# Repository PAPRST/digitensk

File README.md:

# Digital Ten GHz Super Keyer
Modern system for digital mode on 6 and 3cm HAM band

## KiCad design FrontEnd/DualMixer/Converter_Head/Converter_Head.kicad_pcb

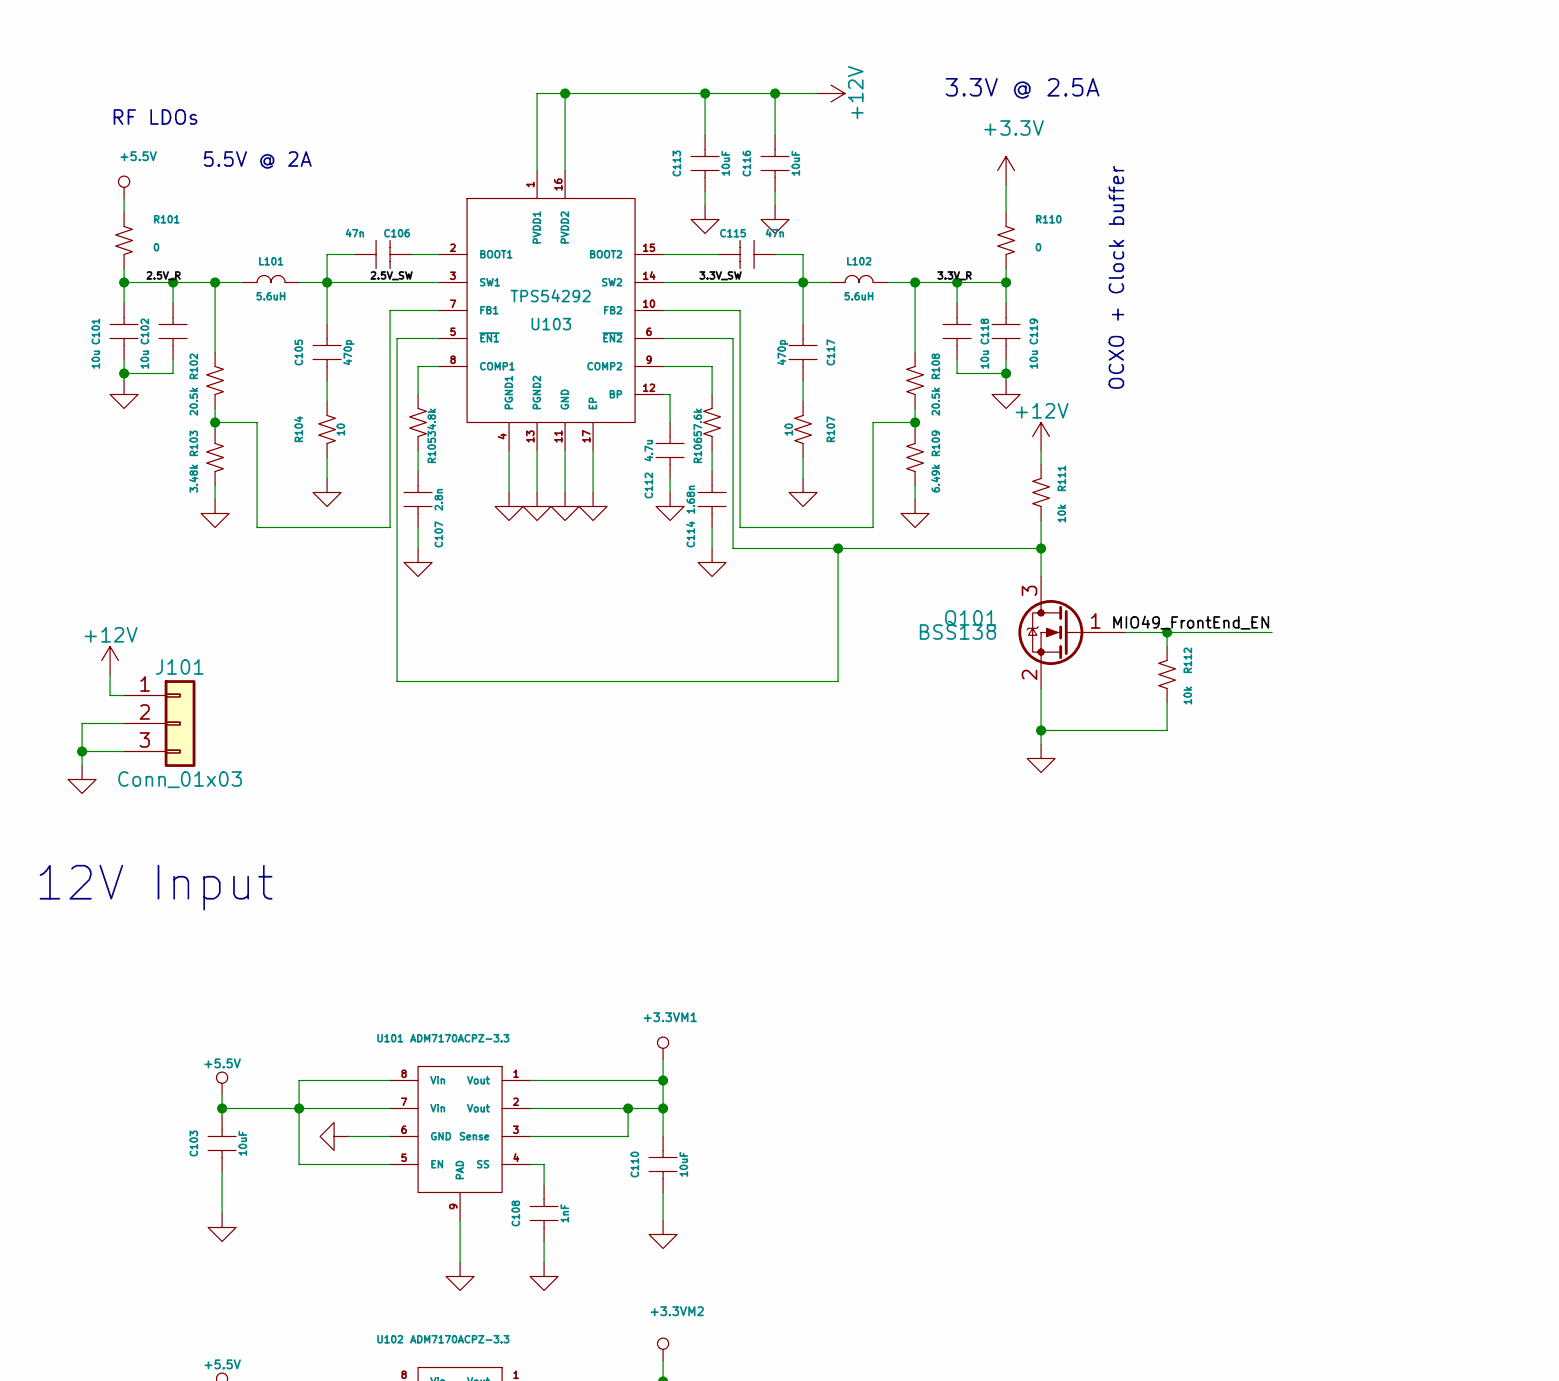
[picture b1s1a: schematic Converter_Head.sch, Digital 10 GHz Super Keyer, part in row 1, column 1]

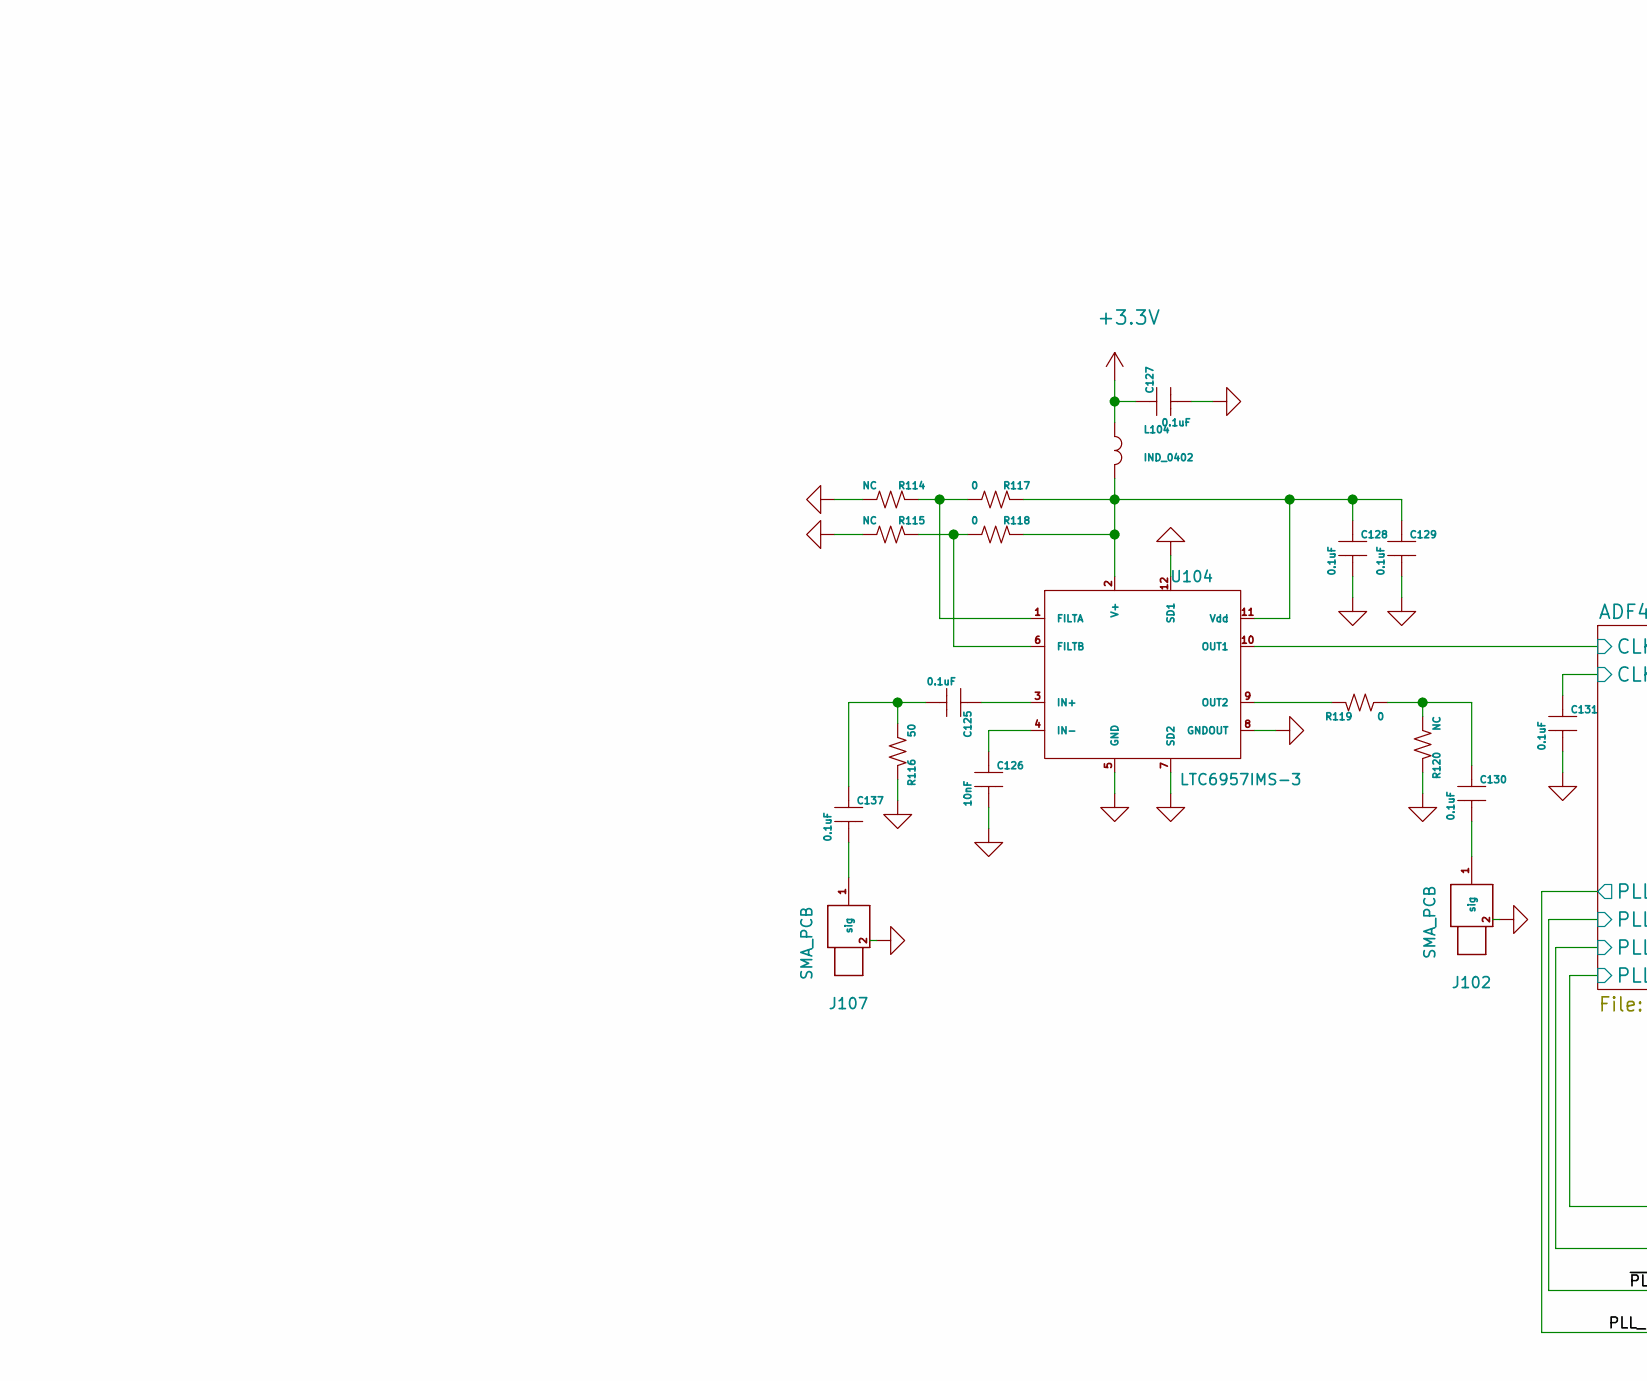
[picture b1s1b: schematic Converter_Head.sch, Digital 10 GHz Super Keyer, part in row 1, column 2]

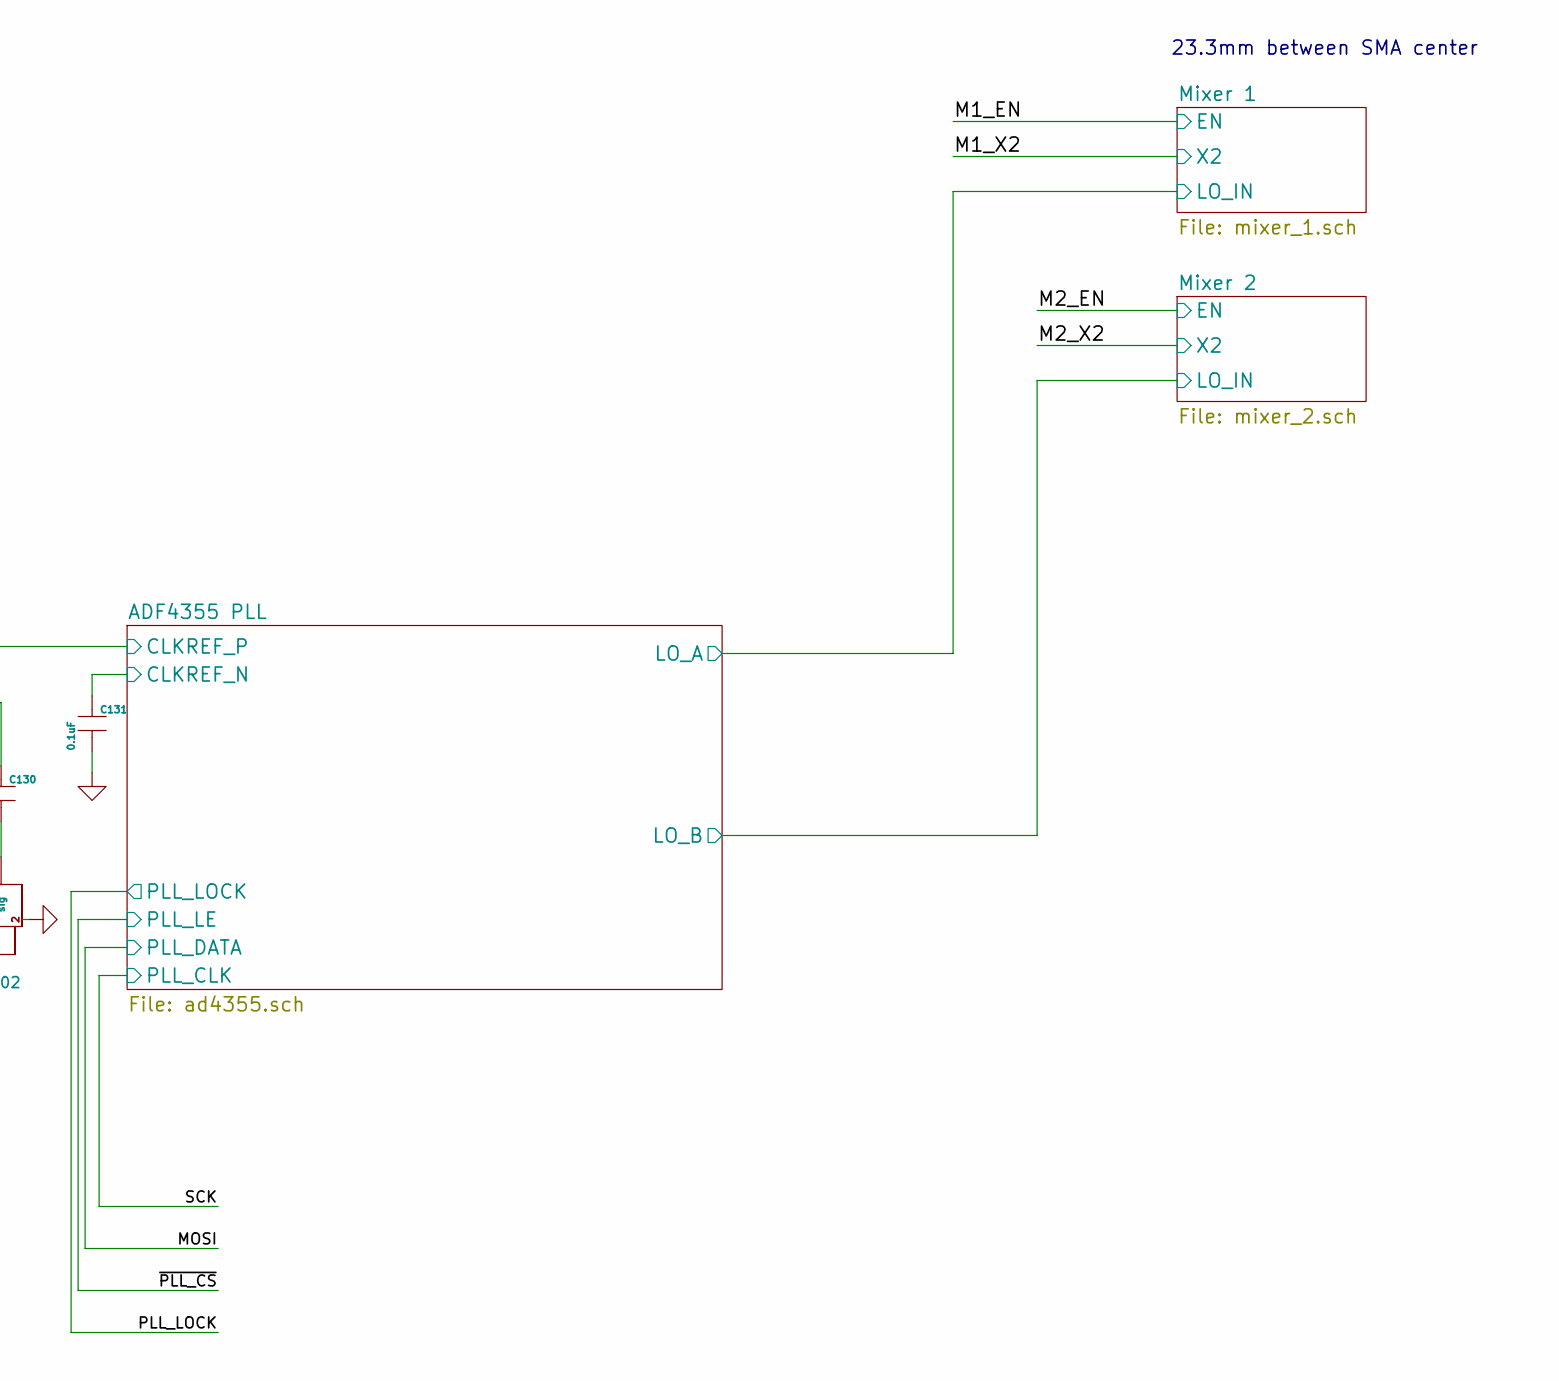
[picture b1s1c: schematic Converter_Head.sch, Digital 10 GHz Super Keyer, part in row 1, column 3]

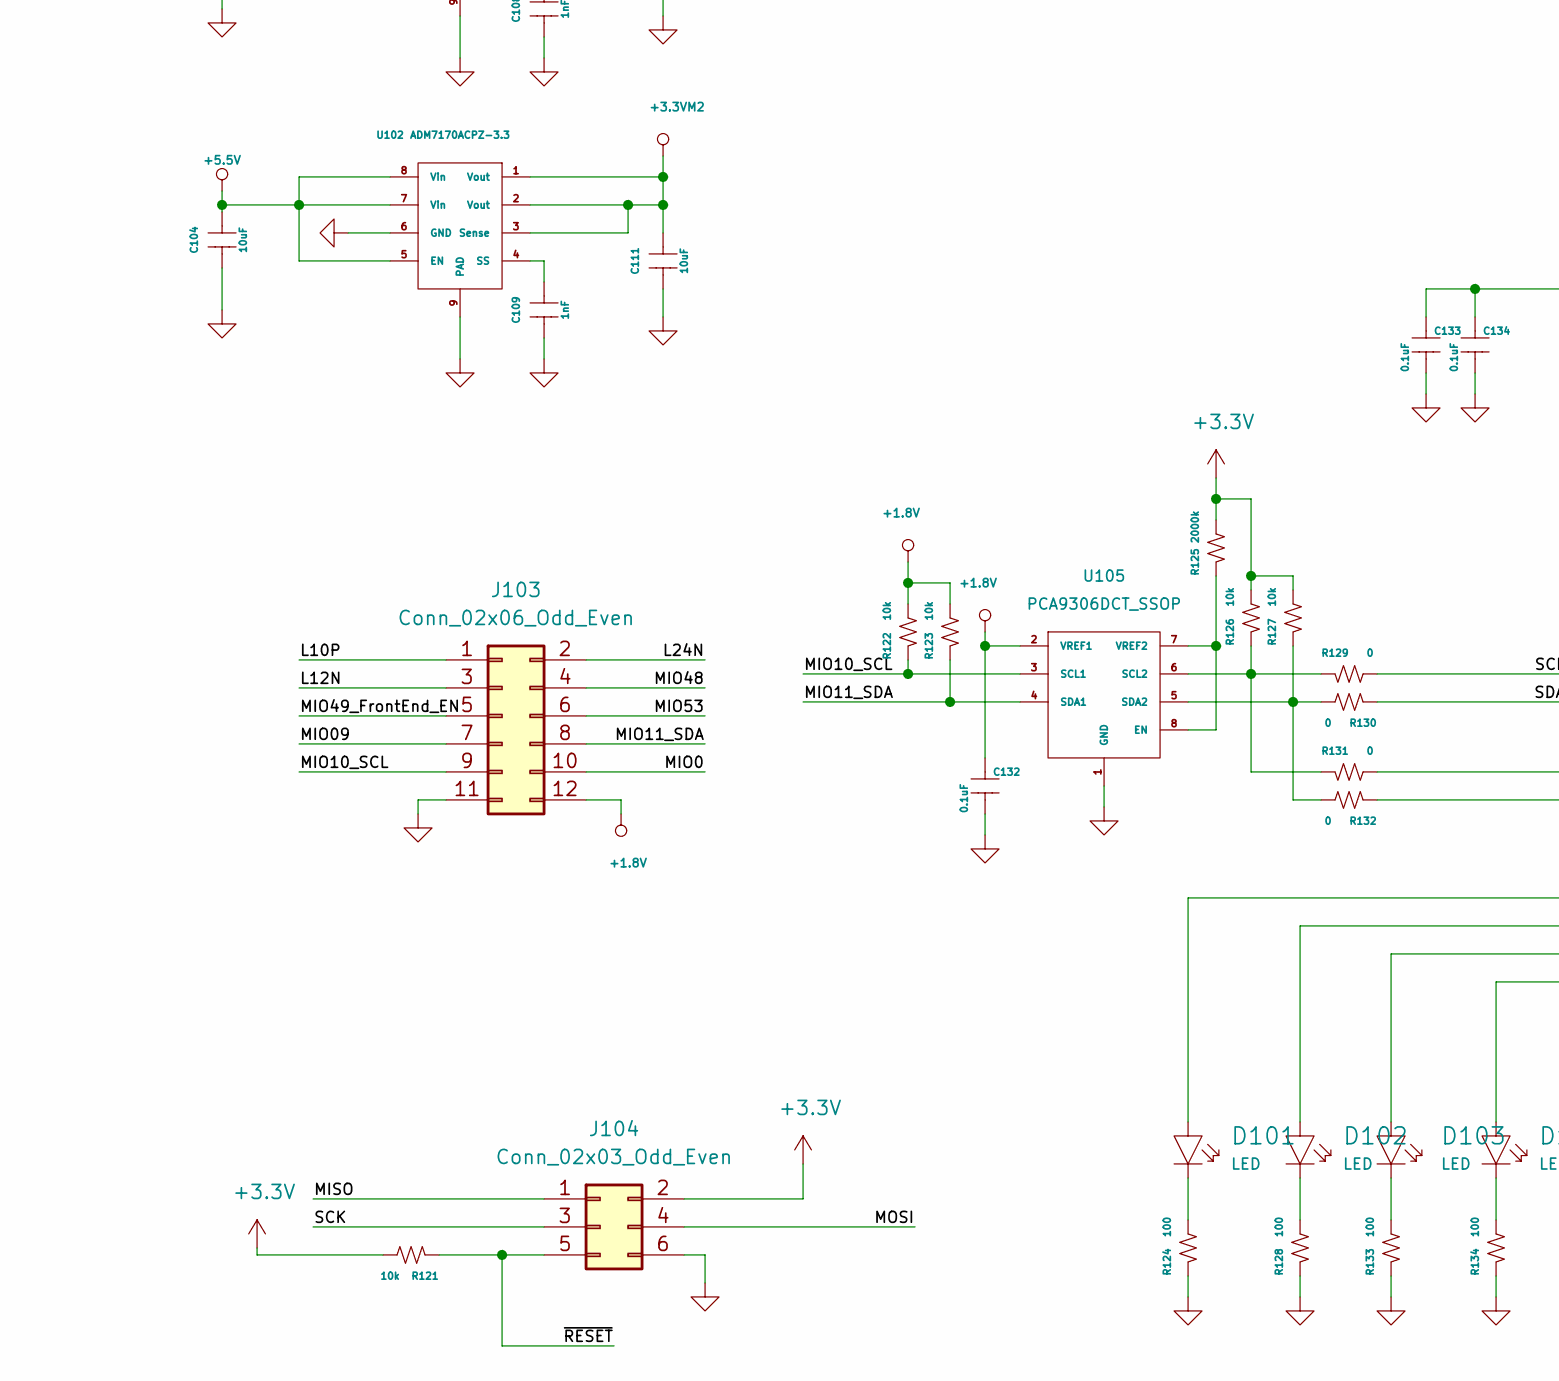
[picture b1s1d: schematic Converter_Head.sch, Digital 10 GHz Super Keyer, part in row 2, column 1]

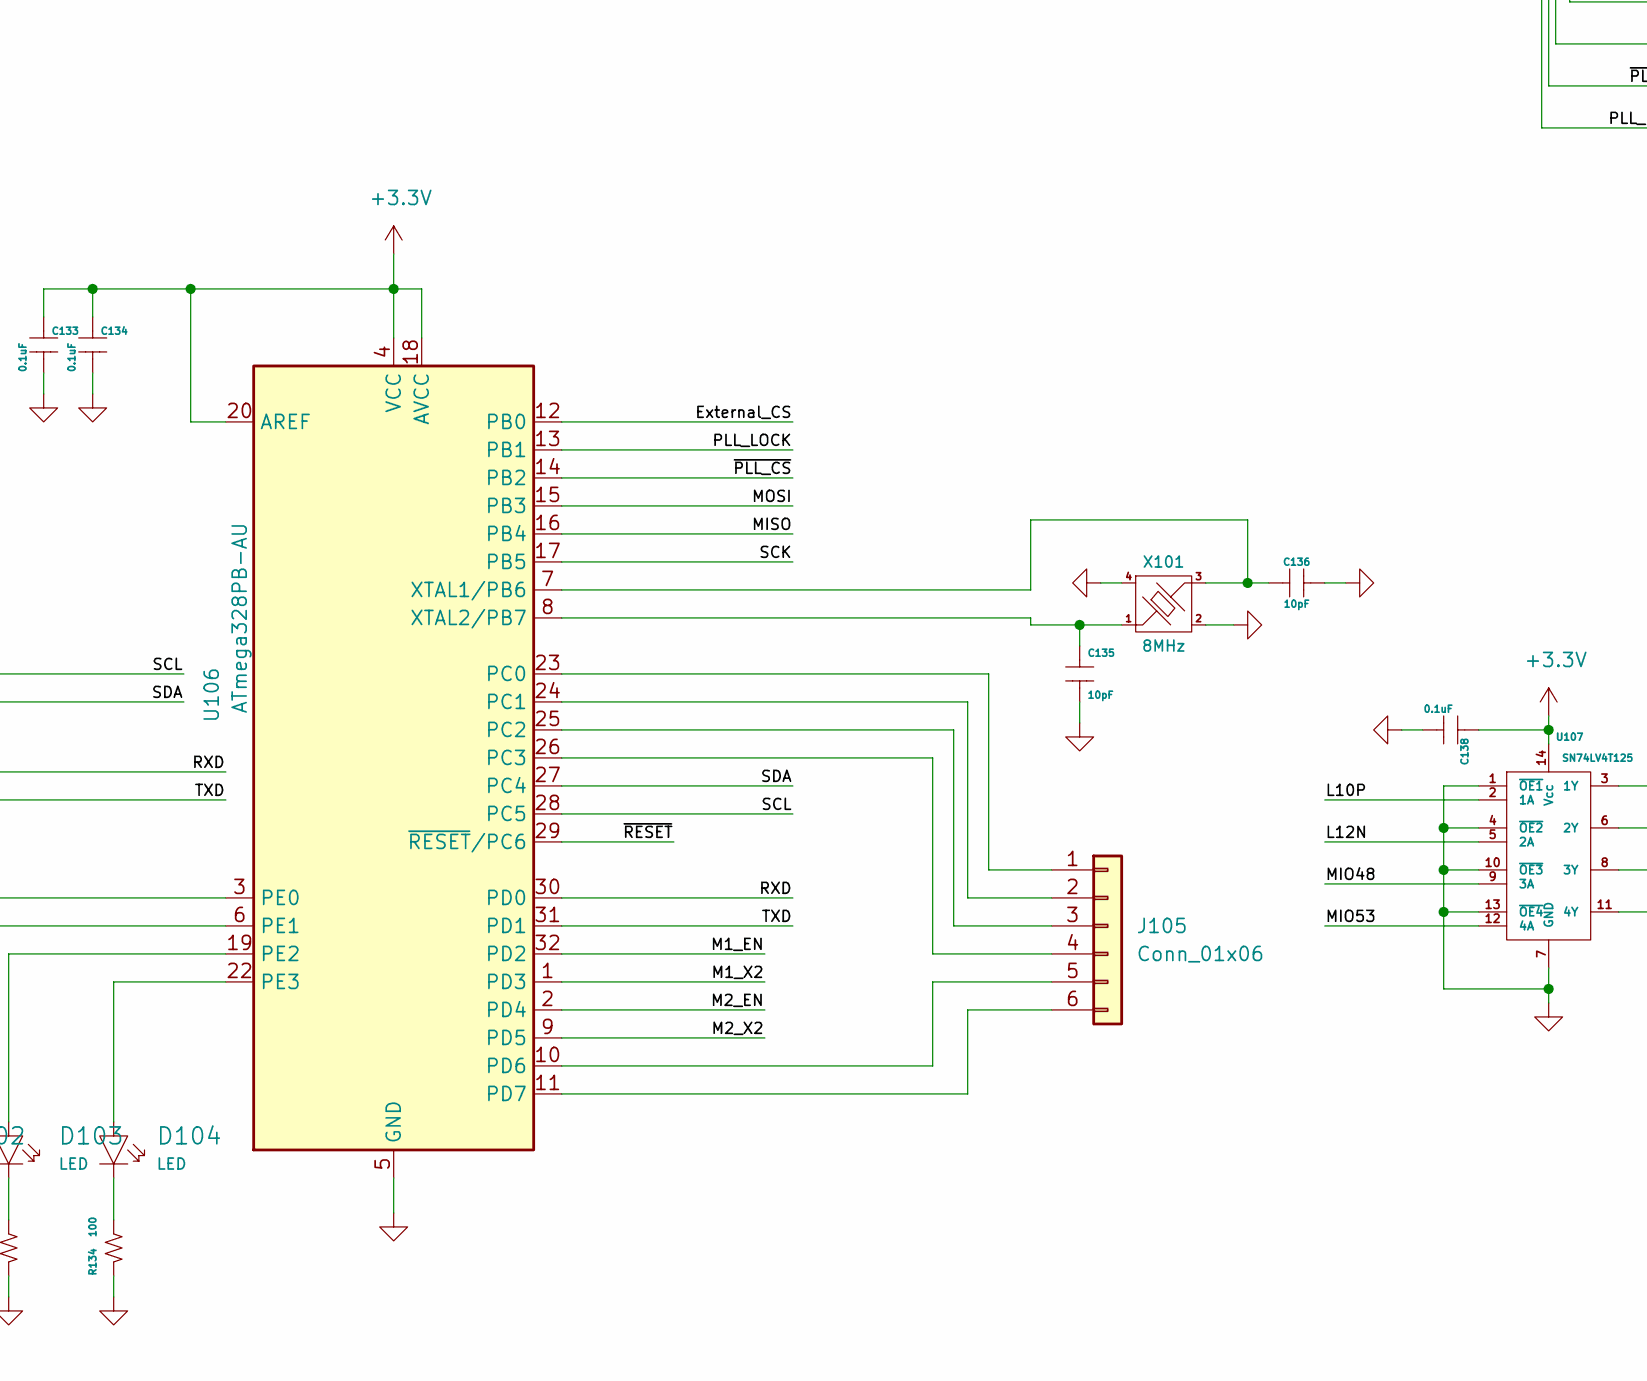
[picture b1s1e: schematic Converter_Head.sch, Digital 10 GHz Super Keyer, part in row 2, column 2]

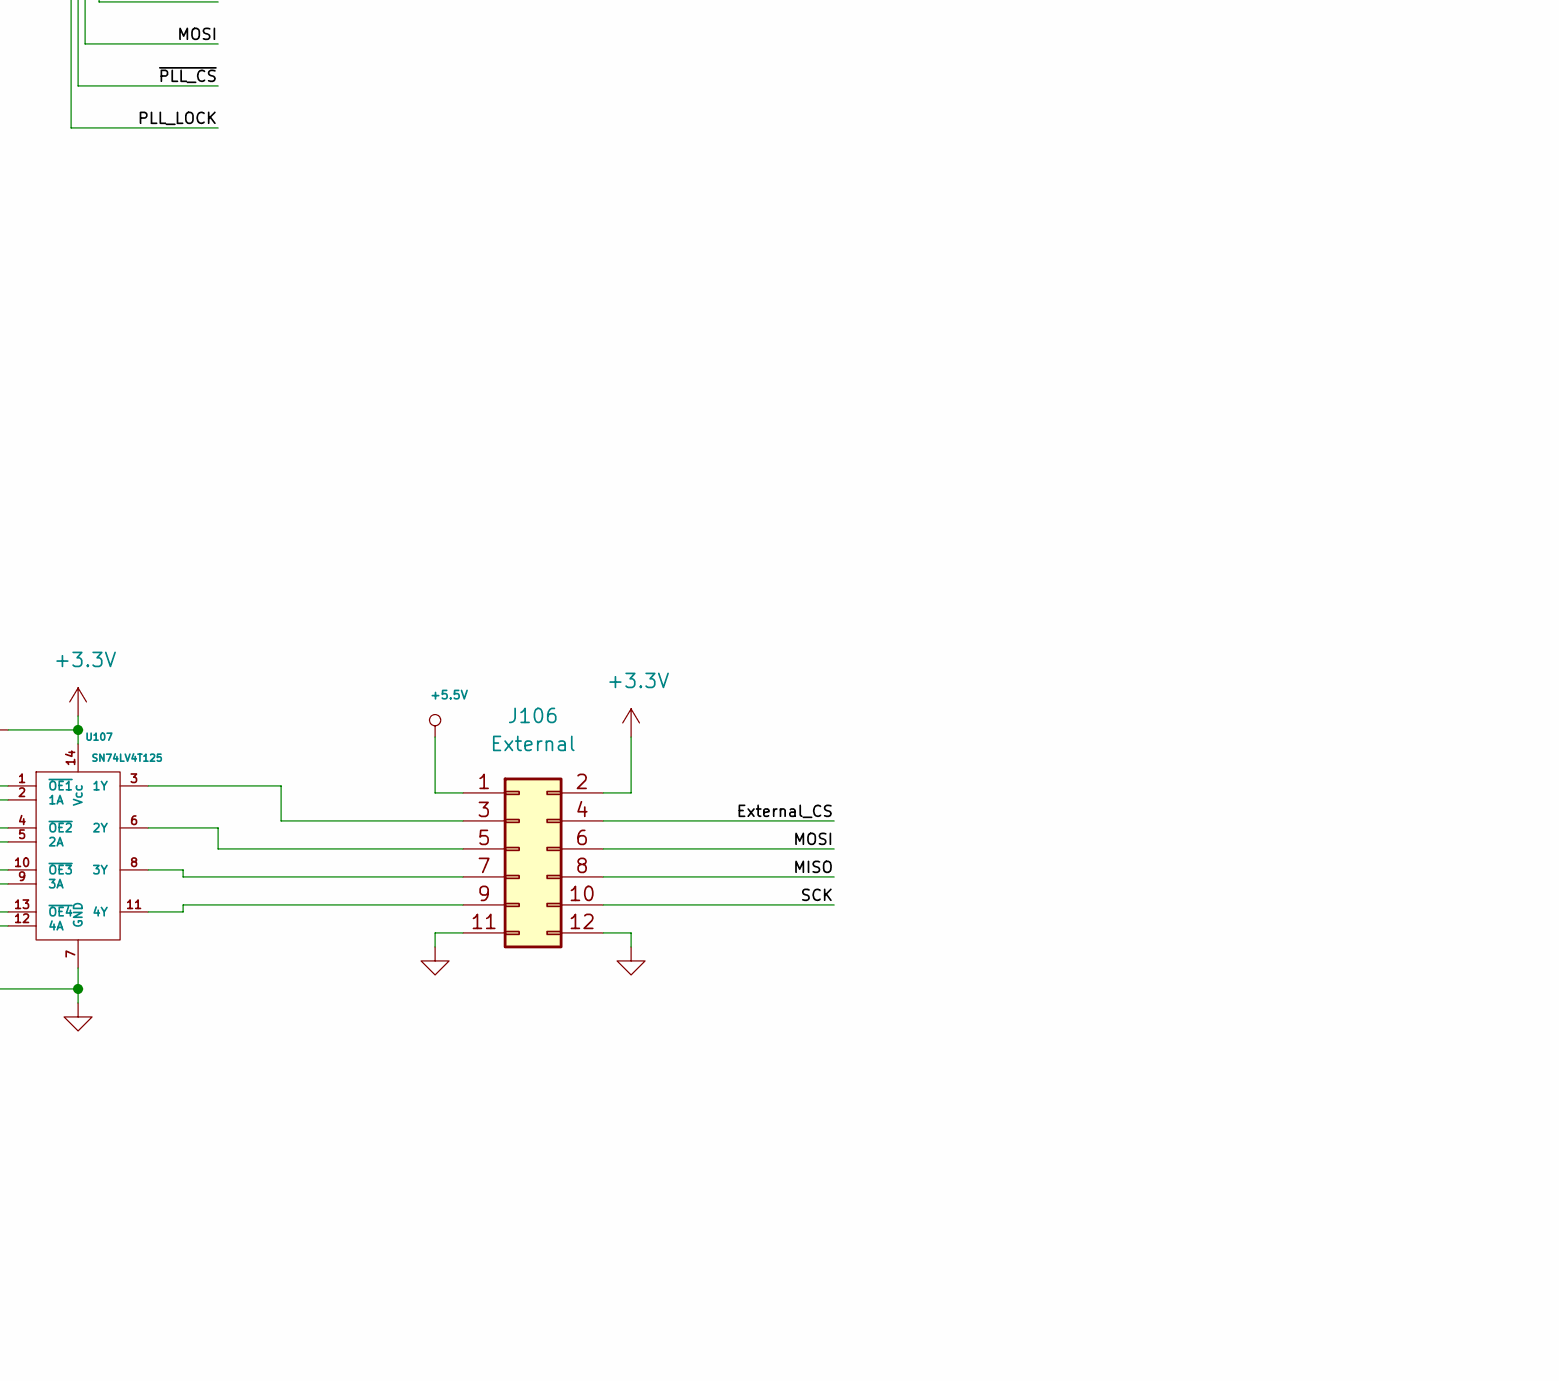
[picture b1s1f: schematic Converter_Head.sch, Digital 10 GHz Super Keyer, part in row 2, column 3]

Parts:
C101, C102, C118, C119: 10u; SM1206
C103, C104, C110, C111: 10uF; SM0805
C105, C117: 470p; SM0603
C106, C115: 47n; SM0603
C107: 2.8n; SM0603
C108, C109: 1nF; SM0603
C112: 4.7u; SM0603
C113, C116: 10uF; SM1206
C114: 1.68n; SM0603
C125, C127, C128, C129, C130, C131, C132, C133, C134, C137, C138: 0.1uF; SM0402
C126: 10nF; SM0402
C135, C136: 10pF; SM0402
D101, D102, D103, D104: LED; LED-0603
J101: Conn_01x03; MOL_CONN_2_VH
J102, J107: SMA_PCB; SMA_RA_PCB_Amphenol
J103: Conn_02x06_Odd_Even; pin_array_6x2
J104: Conn_02x03_Odd_Even; PinHeader_2x03_P2.54mm_Vertical
J105: Conn_01x06; PinHeader_1x06_P2.54mm_Vertical
J106: External; pin_array_6x2
L101, L102: 5.6uH; WE-HCI_SMD_5.6x5.3x4
L104: IND_0402; SM0402
Q101: BSS138; SOT-23
R101, R110: 0; SM1206
R102, R108: 20.5k; SM0603
R103: 3.48k; SM0603
R104, R107: 10; SM0603
R105: 34.8k; SM0603
R106: 57.6k; SM0603
R109: 6.49k; SM0603
R111, R112, R121, R122, R123, R126, R127: 10k; SM0603
R114, R115, R120: NC; SM0402
R116: 50; SM0402
R117, R118, R119: 0; SM0402
R124, R128, R133, R134: 100; SM0603
R125: 2000k; SM0603
R129, R130, R131, R132: 0; SM0603
U101, U102: ADM7170ACPZ-3.3; DFN8_3x3mm
U103: TPS54292; PowerPad_TSSOP_16
U104: LTC6957IMS-3; MSOP-12_3x4mm_P0.65mm
U105: PCA9306DCT_SSOP; SSOP8
U106: ATmega328PB-AU; TQFP-32_7x7mm_P0.8mm
U107: SN74LV4T125; TSSOP-14_4.4x5mm_P0.65mm
X101: 8MHz; xtal_3.2x2.5

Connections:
+1.8V: C132.1, J103.12, R122.2, R123.2, U105.2 (VREF1)
+3.3VM1: C110.1, U101.1 (Vout), U101.2 (Vout), U101.3 (Sense); also elsewhere on the board
+3.3VM2: C111.1, U102.1 (Vout), U102.2 (Vout), U102.3 (Sense); also elsewhere on the board
+3V3: C127.1, C133.1, C134.1, C138.1, J104.2, J106.2, L104.1, R110.1, R121.2, R125.2, R126.2, R127.2, U106.4 (VCC), U106.18 (AVCC), U106.20 (AREF), U107.14 (Vcc)
+5.5V: C103.1, C104.1, J106.1, R101.1, U101.5 (EN), U101.7 (Vin), U101.8 (Vin), U102.5 (EN), U102.7 (Vin), U102.8 (Vin); also elsewhere on the board
+12V: C113.1, C116.1, J101.1, R111.1, U103.1 (PVDD1), U103.16 (PVDD2)
/2.5V_R: C101.1, C102.1, L101.1, R101.2, R102.1
/2.5V_SW: C105.1, C106.1, L101.2, U103.3 (SW1)
/3.3V_R: C118.1, C119.1, L102.1, R108.1, R110.2
/3.3V_SW: C115.1, C117.1, L102.2, U103.14 (SW2)
/ADF4355 PLL/CLKREF_N: C131.1; also elsewhere on the board
/ADF4355 PLL/CLKREF_P: U104.10 (OUT1); also elsewhere on the board
/External_CS: J106.4, U106.12 (PB0)
/L10P: J103.1, U107.2 (1A)
/L12N: J103.3, U107.5 (2A)
/L24N: J103.2
/M1_EN: U106.32 (PD2); also elsewhere on the board
/M1_X2: U106.1 (PD3); also elsewhere on the board
/M2_EN: U106.2 (PD4); also elsewhere on the board
/M2_X2: U106.9 (PD5); also elsewhere on the board
/MIO0: J103.10
/MIO09: J103.7
/MIO10_SCL: J103.9, R122.1, U105.3 (SCL1)
/MIO11_SDA: J103.8, R123.1, U105.4 (SDA1)
/MIO48: J103.4, U107.9 (3A)
/MIO49_FrontEnd_EN: J103.5, Q101.1 (G), R112.1
/MIO53: J103.6, U107.12 (4A)
/MISO: J104.1, J106.8, U106.16 (PB4)
/MOSI: J104.4, J106.6, U106.15 (PB3); also elsewhere on the board
/PLL_LOCK: U106.13 (PB1); also elsewhere on the board
/RXD: R131.2, U106.30 (PD0)
/SCK: J104.3, J106.10, U106.17 (PB5); also elsewhere on the board
/SCL: R129.2, U106.28 (PC5)
/SDA: R130.1, U106.27 (PC4)
/TXD: R132.1, U106.31 (PD1)
/~PLL_CS: U106.14 (PB2); also elsewhere on the board
/~RESET: J104.5, R121.1, U106.29 (~RESET~/PC6)
GND: C101.2, C102.2, C103.2, C104.2, C107.2, C108.2, C109.2, C110.2, C111.2, C112.2, C113.2, C114.2, C116.2, C118.2, C119.2, C126.2, C127.2, C128.2, C129.2, C131.2, C132.2, C133.2, C134.2, C135.2, C136.2, C138.2, J101.2, J101.3, J102.2, J103.11, J104.6, J106.11, J106.12, J107.2, Q101.2 (S), R103.2, R104.2, R107.2, R109.2, R112.2, R114.1, R115.1, R116.2, R120.2, R124.1, R128.1, R133.1, R134.1, U101.6 (GND), U101.9 (PAD), U102.6 (GND), U102.9 (PAD), U103.4 (PGND1), U103.11 (GND), U103.13 (PGND2), U103.17 (EP), U104.5 (GND), U104.7 (SD2), U104.8 (GNDOUT), U104.12 (SD1), U105.1 (GND), U106.5 (GND), U106.21 (GND), U107.1 (~OE1), U107.4 (~OE2), U107.7 (GND), U107.10 (~OE3), U107.13 (~OE4), X101.2, X101.4; also elsewhere on the board
unnamed: C105.2, R104.1
unnamed: C106.2, U103.2 (BOOT1)
unnamed: C107.1, R105.2
unnamed: C108.1, U101.4 (SS)
unnamed: C109.1, U102.4 (SS)
unnamed: C112.1, U103.12 (BP)
unnamed: C114.1, R106.2
unnamed: C115.2, U103.15 (BOOT2)
unnamed: C117.2, R107.1
unnamed: C125.1, U104.3 (IN+)
unnamed: C125.2, C137.1, R116.1
unnamed: C126.1, U104.4 (IN-)
unnamed: C128.1, C129.1, L104.2, R117.2, R118.2, U104.2 (V+), U104.11 (Vdd)
unnamed: C130.1, R119.1, R120.1
unnamed: C130.2, J102.1 (sig)
unnamed: C135.1, U106.8 (XTAL2/PB7), X101.1
unnamed: C136.1, U106.7 (XTAL1/PB6), X101.3
unnamed: C137.2, J107.1 (sig)
unnamed: D101.A, U106.3 (PE0)
unnamed: D101.K, R124.2
unnamed: D102.A, U106.6 (PE1)
unnamed: D102.K, R128.2
unnamed: D103.A, U106.19 (PE2)
unnamed: D103.K, R133.2
unnamed: D104.A, U106.22 (PE3)
unnamed: D104.K, R134.2
unnamed: J105.1, U106.23 (PC0)
unnamed: J105.2, U106.24 (PC1)
unnamed: J105.3, U106.25 (PC2)
unnamed: J105.4, U106.26 (PC3)
unnamed: J105.5, U106.10 (PD6)
unnamed: J105.6, U106.11 (PD7)
unnamed: J106.3, U107.3 (1Y)
unnamed: J106.5, U107.6 (2Y)
unnamed: J106.7, U107.8 (3Y)
unnamed: J106.9, U107.11 (4Y)
unnamed: Q101.3 (D), R111.2, U103.5 (~EN1), U103.6 (~EN2)
unnamed: R102.2, R103.1, U103.7 (FB1)
unnamed: R105.1, U103.8 (COMP1)
unnamed: R106.1, U103.9 (COMP2)
unnamed: R108.2, R109.1, U103.10 (FB2)
unnamed: R114.2, R117.1, U104.1 (FILTA)
unnamed: R115.2, R118.1, U104.6 (FILTB)
unnamed: R119.2, U104.9 (OUT2)
unnamed: R125.1, U105.7 (VREF2), U105.8 (EN)
unnamed: R126.1, R129.1, R131.1, U105.6 (SCL2)
unnamed: R127.1, R130.2, R132.2, U105.5 (SDA2)

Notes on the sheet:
12V Input
3.3V @ 2.5A
OCXO + Clock buffer
RF LDOs
5.5V @ 2A
23.3mm between SMA center

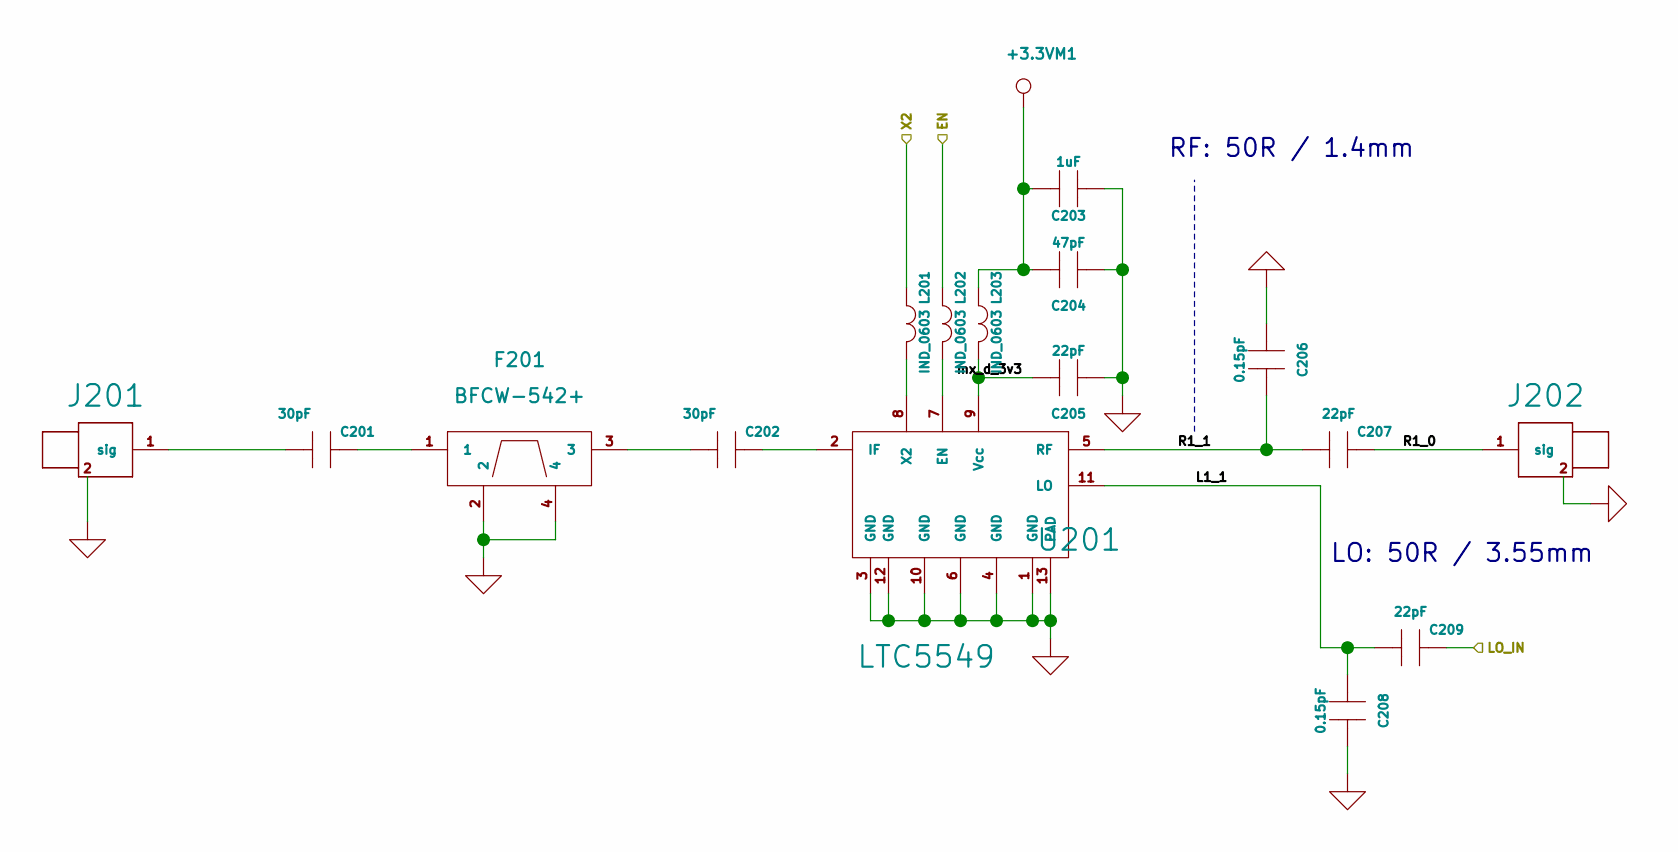
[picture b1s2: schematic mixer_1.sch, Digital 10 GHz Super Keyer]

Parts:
C201, C202: 30pF; SM0402
C203: 1uF; SM0603
C204: 47pF; SM0402
C205, C207, C209: 22pF; SM0402
C206, C208: 0.15pF; SM0402
F201: BFCW-542+
J201, J202: SMA_PCB; PAD_T_200x110um
L201, L202, L203: IND_0603; SM0603
U201: LTC5549; QFN12_2x3mm_UDB_LT

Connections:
+3.3VM1: C203.1, C204.2, L203.2; also elsewhere on the board
/ADF4355 PLL/LO_A: C209.1; also elsewhere on the board
/M1_EN: L202.2; also elsewhere on the board
/M1_X2: L201.2; also elsewhere on the board
/Mixer 1/L1_1: C208.1, C209.2, U201.11 (LO)
/Mixer 1/R1_0: C207.1, J202.1 (sig)
/Mixer 1/R1_1: C206.2, C207.2, U201.5 (RF)
/Mixer 1/mx_d_3v3: C205.2, L203.1, U201.9 (Vcc)
GND: C203.2, C204.1, C205.1, C206.1, C208.2, F201.2, F201.4, J201.2, J202.2, U201.1 (GND), U201.3 (GND), U201.4 (GND), U201.6 (GND), U201.10 (GND), U201.12 (GND), U201.13 (PAD); also elsewhere on the board
unnamed: C201.1, F201.1
unnamed: C201.2, J201.1 (sig)
unnamed: C202.1, U201.2 (IF)
unnamed: C202.2, F201.3
unnamed: L201.1, U201.8 (X2)
unnamed: L202.1, U201.7 (EN)

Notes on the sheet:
LO: 50R / 3.55mm
RF: 50R / 1.4mm

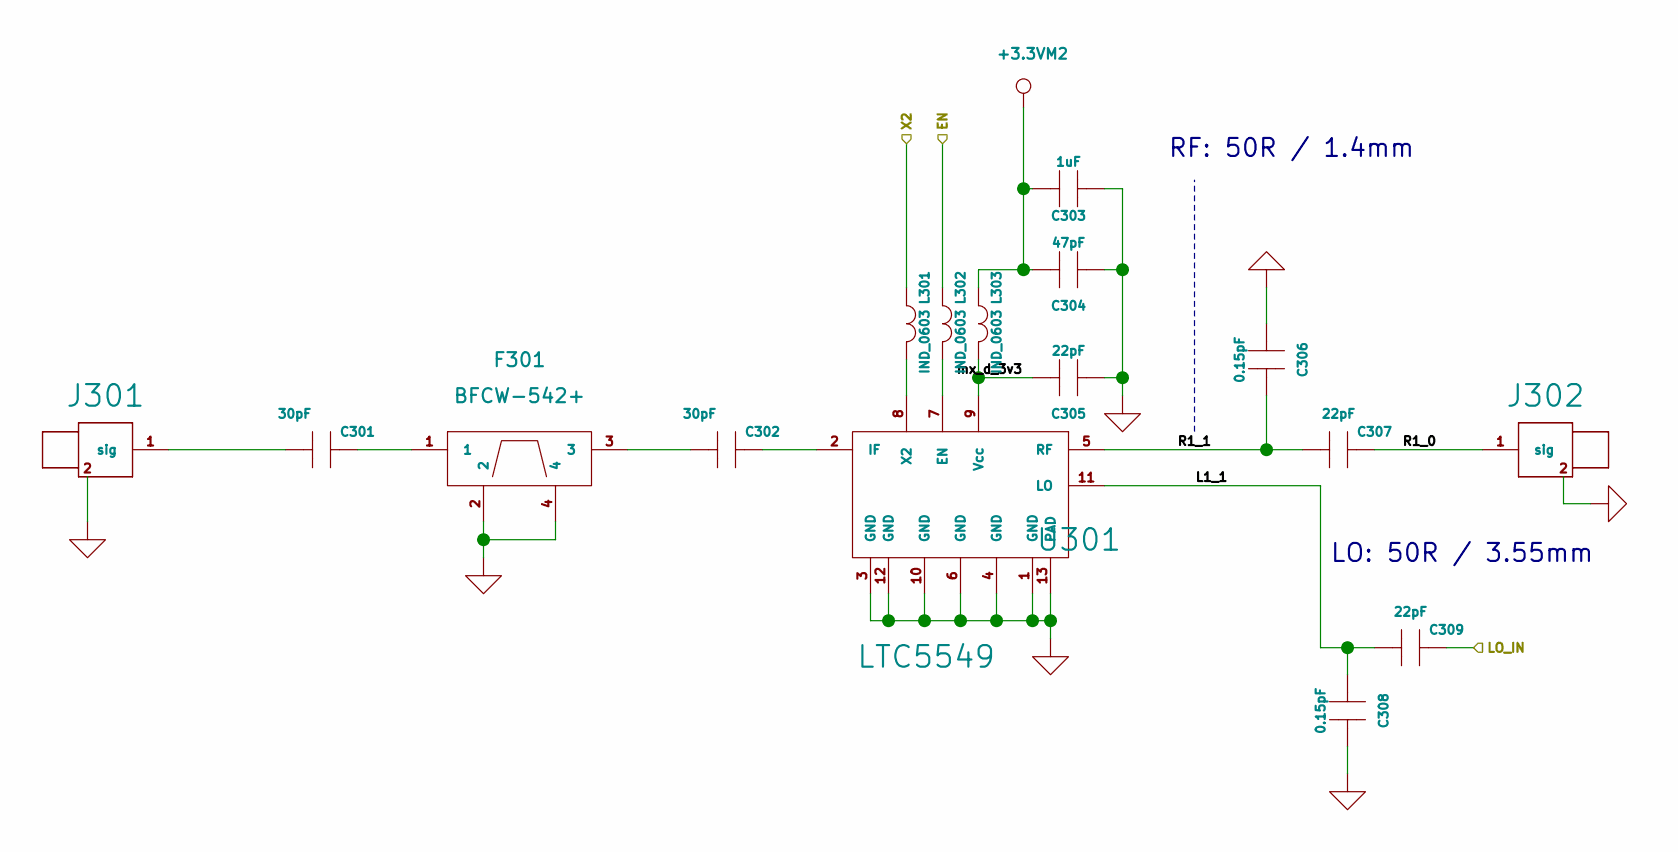
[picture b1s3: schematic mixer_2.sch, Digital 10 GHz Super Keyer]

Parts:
C301, C302: 30pF; SM0402
C303: 1uF; SM0603
C304: 47pF; SM0402
C305, C307, C309: 22pF; SM0402
C306, C308: 0.15pF; SM0402
F301: BFCW-542+
J301, J302: SMA_PCB; PAD_T_200x110um
L301, L302, L303: IND_0603; SM0603
U301: LTC5549; QFN12_2x3mm_UDB_LT

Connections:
+3.3VM2: C303.1, C304.2, L303.2; also elsewhere on the board
/ADF4355 PLL/LO_B: C309.1; also elsewhere on the board
/M2_EN: L302.2; also elsewhere on the board
/M2_X2: L301.2; also elsewhere on the board
/Mixer 2/L1_1: C308.1, C309.2, U301.11 (LO)
/Mixer 2/R1_0: C307.1, J302.1 (sig)
/Mixer 2/R1_1: C306.2, C307.2, U301.5 (RF)
/Mixer 2/mx_d_3v3: C305.2, L303.1, U301.9 (Vcc)
GND: C303.2, C304.1, C305.1, C306.1, C308.2, F301.2, F301.4, J301.2, J302.2, U301.1 (GND), U301.3 (GND), U301.4 (GND), U301.6 (GND), U301.10 (GND), U301.12 (GND), U301.13 (PAD); also elsewhere on the board
unnamed: C301.1, F301.1
unnamed: C301.2, J301.1 (sig)
unnamed: C302.1, U301.2 (IF)
unnamed: C302.2, F301.3
unnamed: L301.1, U301.8 (X2)
unnamed: L302.1, U301.7 (EN)

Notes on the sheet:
LO: 50R / 3.55mm
RF: 50R / 1.4mm
